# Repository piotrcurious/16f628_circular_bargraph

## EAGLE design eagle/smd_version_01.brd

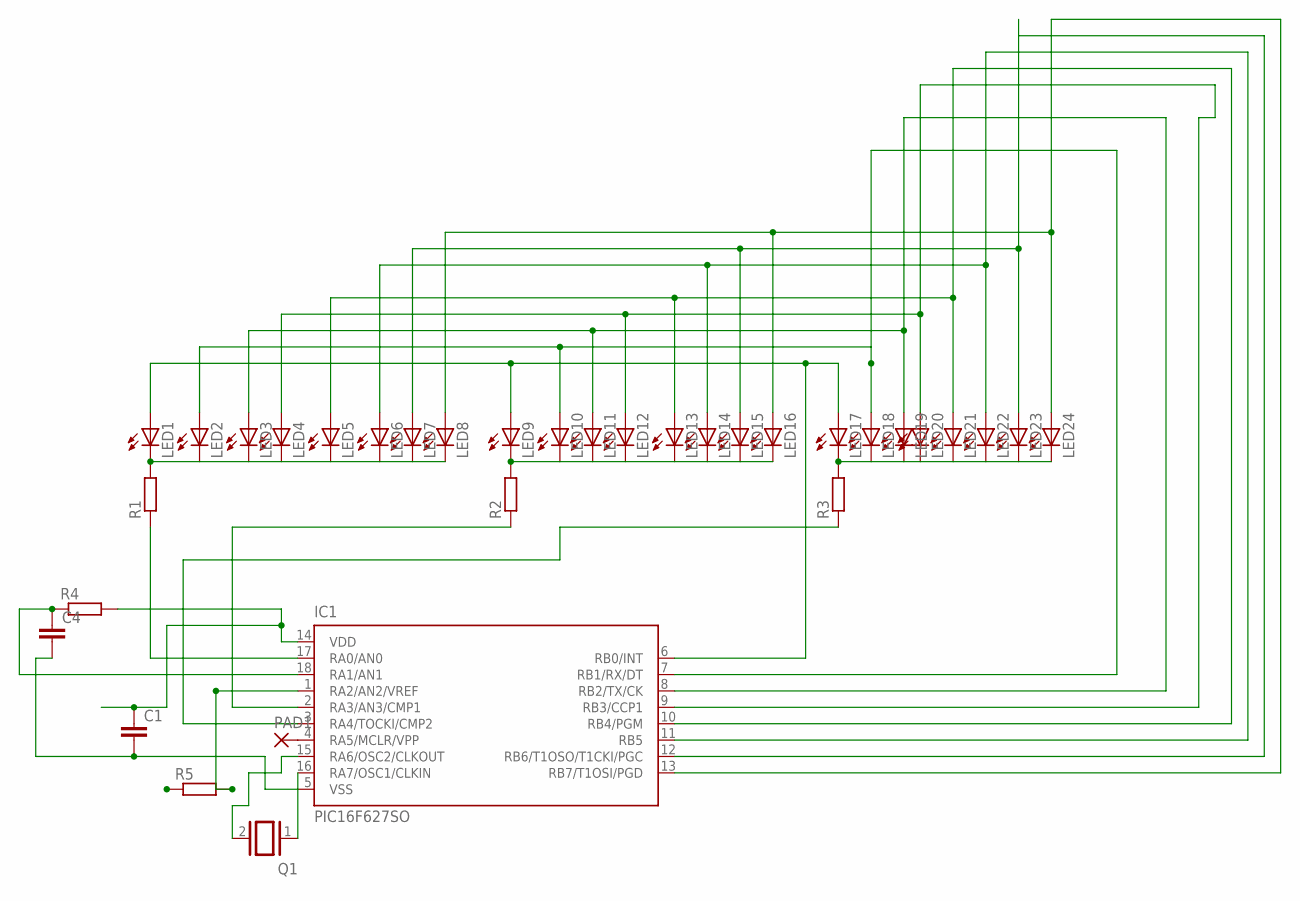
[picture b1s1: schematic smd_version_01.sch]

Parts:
C1: C-EUC1825; C1825
C4: C-EUC0805; C0805
IC1: PIC16F627SO; SO-18W
LED1, LED2, LED3, LED4, LED5, LED6, LED7, LED8, LED9, LED10, LED11, LED12, LED13, LED14, LED15, LED16, LED17, LED18, LED19, LED20, LED21, LED22, LED23, LED24: LEDSMT1206; 1206
PAD1: SMD2; SMD1,27-2,54
Q1: XTAL/S; QS
R1, R2, R3: R-EU_0207/15; 0207/15
R4: R-EU_M1406; M1406
R5: R-EU_0207/12; 0207/12

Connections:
unnamed: LED1.C, LED2.C, LED3.C, LED4.C, LED5.C, LED6.C, LED7.C, LED8.C, R1.2
unnamed: LED9.C, LED10.C, LED11.C, LED12.C, LED13.C, LED14.C, LED15.C, LED16.C, R2.2
unnamed: LED17.C, LED18.C, LED19.C, LED20.C, LED21.C, LED22.C, LED23.C, LED24.C, R3.2
unnamed: IC1.17 (RA0/AN0), R1.1
unnamed: IC1.2 (RA3/AN3/CMP1), R2.1
unnamed: IC1.3 (RA4/TOCKI/CMP2), R3.1
unnamed: IC1.6 (RB0/INT), LED1.A, LED9.A, LED17.A
unnamed: IC1.7 (RB1/RX/DT), LED2.A, LED10.A, LED18.A
unnamed: IC1.8 (RB2/TX/CK), LED3.A, LED11.A, LED19.A
unnamed: IC1.9 (RB3/CCP1), LED4.A, LED12.A, LED20.A
unnamed: IC1.10 (RB4/PGM), LED5.A, LED13.A, LED21.A
unnamed: IC1.11 (RB5), LED6.A, LED14.A, LED22.A
unnamed: IC1.12 (RB6/T1OSO/T1CKI/PGC), LED7.A, LED15.A, LED23.A
unnamed: IC1.13 (RB7/T1OSI/PGD), LED8.A, LED16.A, LED24.A
unnamed: IC1.4 (RA5/MCLR/VPP), PAD1.1
unnamed: IC1.16 (RA7/OSC1/CLKIN), Q1.1
unnamed: IC1.15 (RA6/OSC2/CLKOUT), Q1.2
unnamed: C1.1, IC1.14 (VDD), R4.2
unnamed: C1.2, C4.2, IC1.5 (VSS)
unnamed: C4.1, IC1.18 (RA1/AN1), R4.1
unnamed: IC1.1 (RA2/AN2/VREF), R5.2

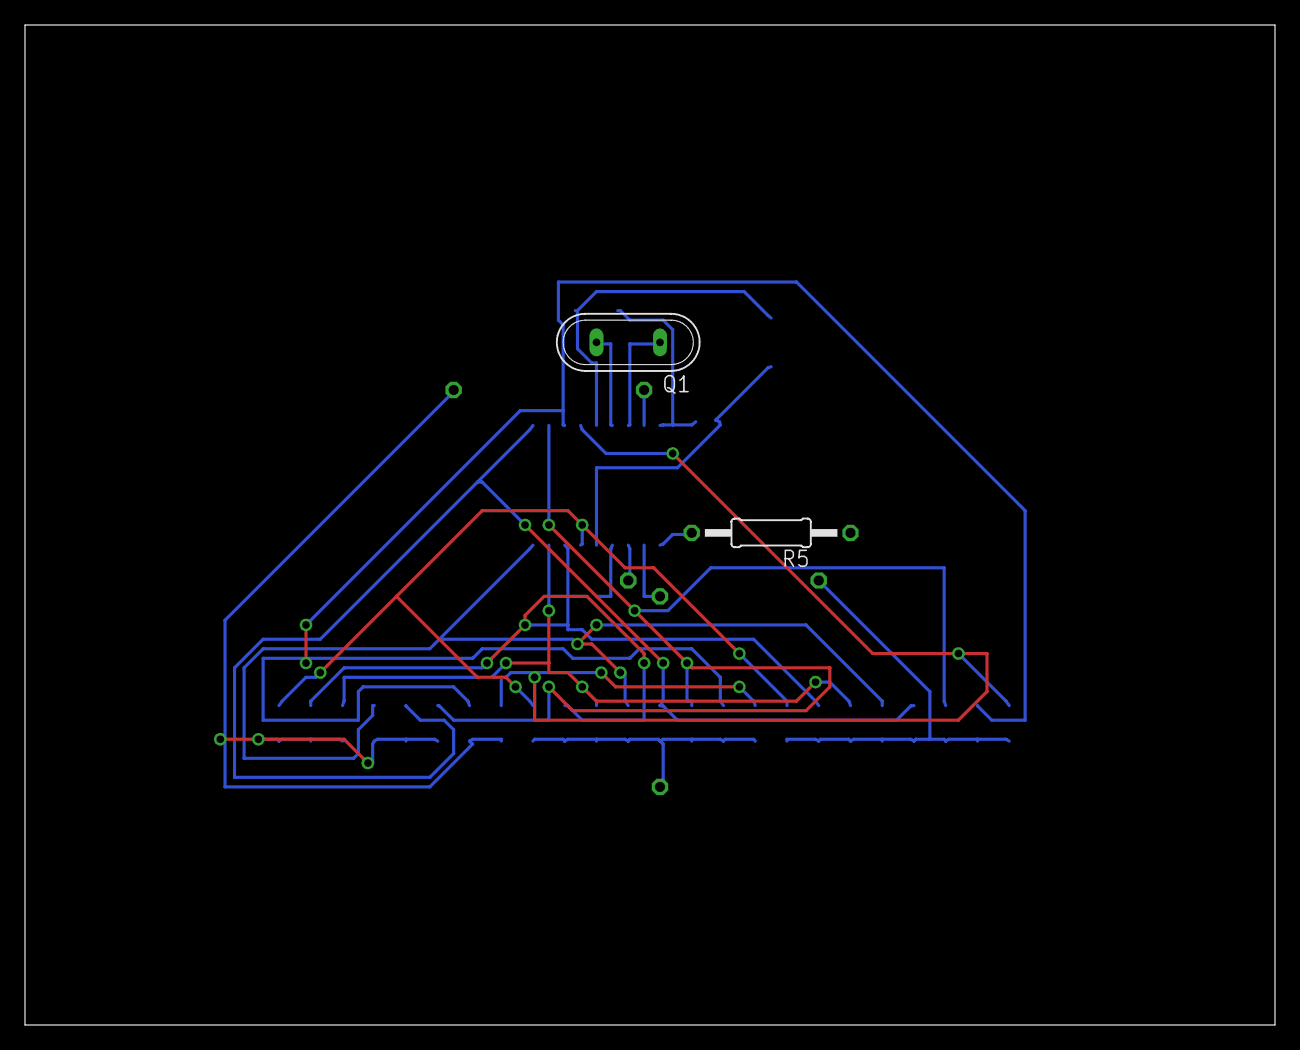
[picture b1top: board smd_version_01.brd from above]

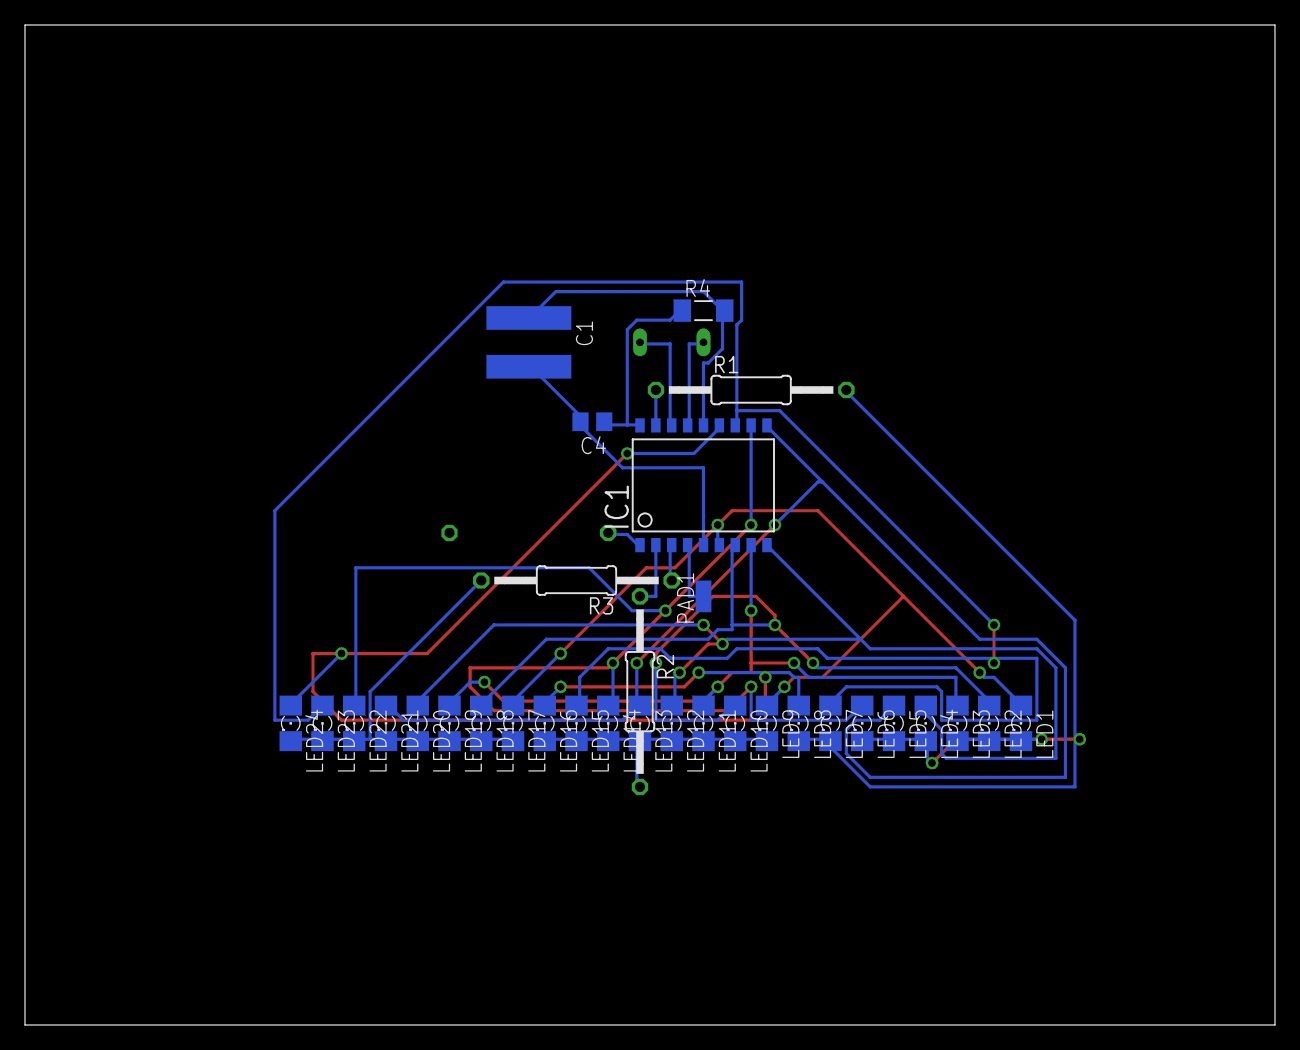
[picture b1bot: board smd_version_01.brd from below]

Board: 2 copper layers, 100.0 x 80.0 mm, 34 parts (32 on the bottom side), 21 nets.

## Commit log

2022-10-25 whole release
    old release
2022-10-25 added old files
